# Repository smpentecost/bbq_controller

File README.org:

View this project on [CADLAB.io](https://cadlab.io/project/23533). 

* Automated BBQ Controller

This project brings my BBQ/smoker into the 21st century, by automating control of its airflow damper based on the smoker's current temperature. My parts list:

1. 1x Raspberry Pi Zero W - $10
2. 1x SD card loaded with Raspbian Lite - $5
3. 2x SainSmart MAX6675 Module + K Type Thermocouple Thermocouple Sensor Temperature 0~1024℃ - $14ea
4. 1x Futaba S3003 Servo - $18
5. 1x 5-in HVAC Damper Duct Manual Volume Damper with Sleeve - $15
6. 1x MCIGICM IC 7805 Voltage Regulator, L7805 Linear Positive Fixed 1 Output 5V 1.5A - $0.50ea
7. 1x Custom adapter board - Free since I had parts laying around
8. 1x 9V 1A Power Supply - $10

Pictures of the adapter board details to come soon.

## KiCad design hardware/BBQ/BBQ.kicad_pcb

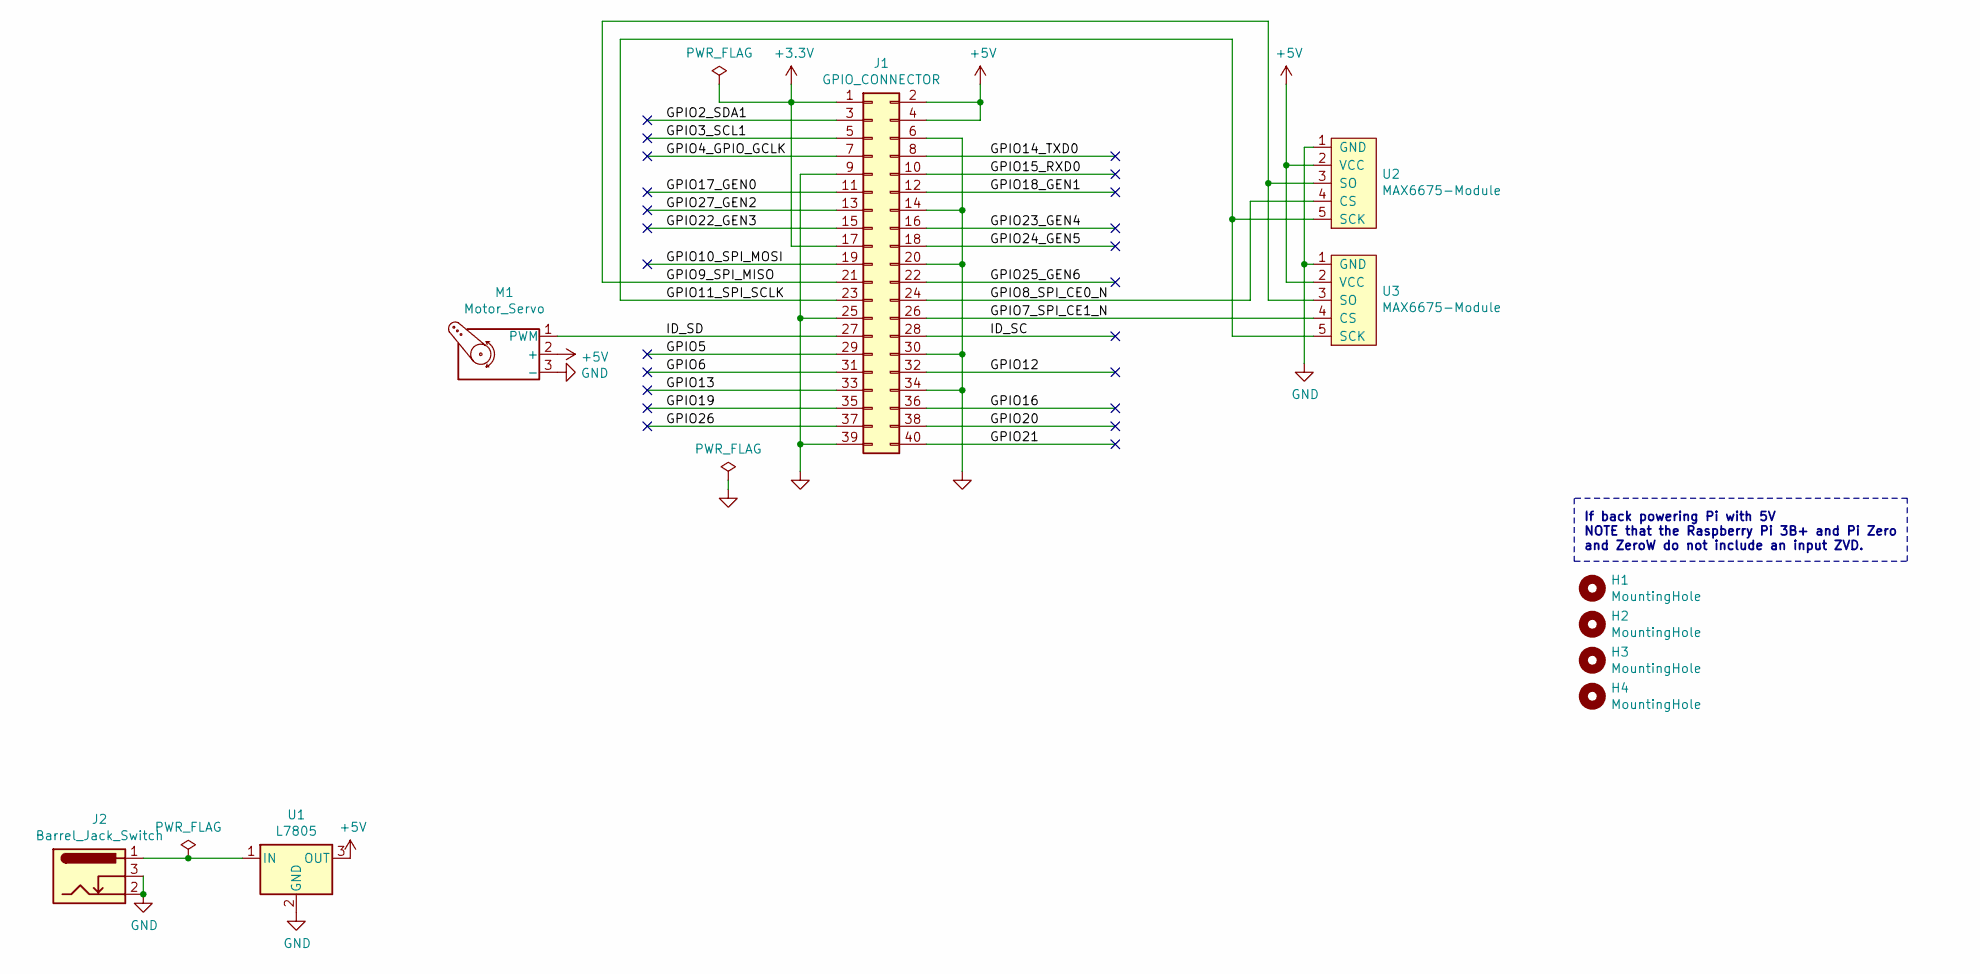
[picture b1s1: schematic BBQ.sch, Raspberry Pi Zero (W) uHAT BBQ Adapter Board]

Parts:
H1, H2, H3, H4: MountingHole; MountingHole_2.7mm_M2.5_uHAT_RPi
J1: GPIO_CONNECTOR; PinSocket_2x20_P2.54mm_Vertical_Centered_Anchor
J2: Barrel_Jack_Switch; TestPoint_2Pads_Pitch5.08mm_Drill1.3mm
M1: Motor_Servo; PinHeader_1x03_P2.54mm_Vertical
U1: L7805; TO-220-3_Horizontal_TabDown
U2, U3: MAX6675-Module; PinHeader_1x05_P2.54mm_Vertical

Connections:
+3V3: J1.1, J1.17
+5V: J1.2, J1.4, M1.2 (+), U1.3 (OUT), U2.2 (VCC), U3.2 (VCC)
/GPIO2_SDA1: J1.3
/GPIO3_SCL1: J1.5
/GPIO4_GPIO_GCLK: J1.7
/GPIO5: J1.29
/GPIO6: J1.31
/GPIO7_SPI_CE1_N: J1.26, U3.4 (CS)
/GPIO8_SPI_CE0_N: J1.24, U2.4 (CS)
/GPIO9_SPI_MISO: J1.21, U2.3 (SO), U3.3 (SO)
/GPIO10_SPI_MOSI: J1.19
/GPIO11_SPI_SCLK: J1.23, U2.5 (SCK), U3.5 (SCK)
/GPIO12: J1.32
/GPIO13: J1.33
/GPIO14_TXD0: J1.8
/GPIO15_RXD0: J1.10
/GPIO16: J1.36
/GPIO17_GEN0: J1.11
/GPIO18_GEN1: J1.12
/GPIO19: J1.35
/GPIO20: J1.38
/GPIO21: J1.40
/GPIO22_GEN3: J1.15
/GPIO23_GEN4: J1.16
/GPIO24_GEN5: J1.18
/GPIO25_GEN6: J1.22
/GPIO26: J1.37
/GPIO27_GEN2: J1.13
/ID_SC: J1.28
/ID_SD: J1.27, M1.1 (PWM)
GND: J1.6, J1.9, J1.14, J1.20, J1.25, J1.30, J1.34, J1.39, J2.2, J2.3, M1.3 (-), U1.2 (GND), U2.1 (GND), U3.1 (GND)
unnamed: J2.1, U1.1 (IN)

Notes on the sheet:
If back powering Pi with 5V NOTE that the Raspberry Pi 3B+ and Pi Zero and ZeroW do not include an input ZVD.

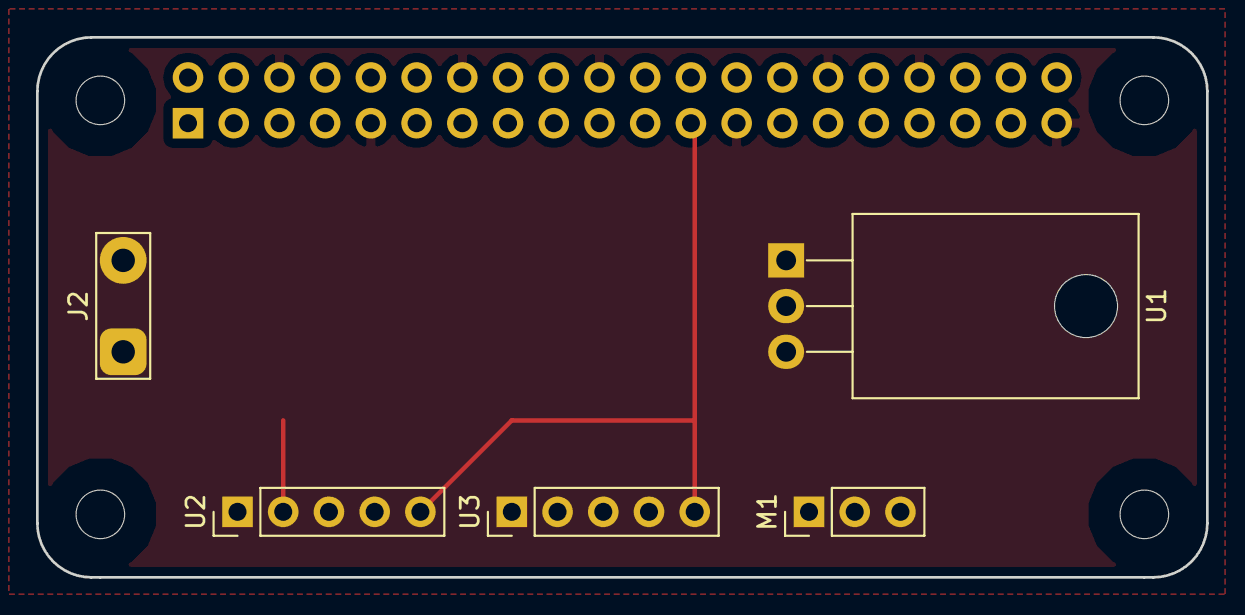
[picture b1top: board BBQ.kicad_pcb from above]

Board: 2 copper layers, 65.0 x 30.0 mm, 10 parts (1 on the bottom side), 9 nets.

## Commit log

2020-02-29 controller working with spi and servo
2020-06-06 Dumb Controller
2020-06-07 added README.org
2020-06-07 refresh README
2020-06-07 Create LICENSE
2020-06-11 reorganized files
2020-06-11 more conscise init for the controller
2020-06-23 psql reorg
2020-07-03 sending temps to database
2020-11-17 added hardware folder
2020-11-17 added hardware
2020-11-17 Backlink to CADLAB.io has been added.
2020-11-17 reorg

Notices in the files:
hardware/BBQ/BBQ.kicad_pcb:
This PCB design is licensed under MIT Open Source License.
hardware/BBQ/BBQ.sch:
This Schematic is licensed under MIT Open Source License.
